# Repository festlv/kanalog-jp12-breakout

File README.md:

KFlop KAnalog JP12 breakout
==================================

KAnalog board has a connector JP12 with 8 outputs and 8 inputs. Since these IOs are unprotected, 3.3V LVTTL type, they 
are less than suitable for use for general purpose tasks (extra end stops, outputs etc).

This board breaks out these IOs as opto-isolated inputs and outputs, suitable for driving 24V loads and reading 24V inputs.

IO connection follows Kconnect conventions, see optoisolated inputs/outputs section of [this document](http://dynomotion.com/Help/SchematicsKonnect/ConnectorsKonnect.htm).

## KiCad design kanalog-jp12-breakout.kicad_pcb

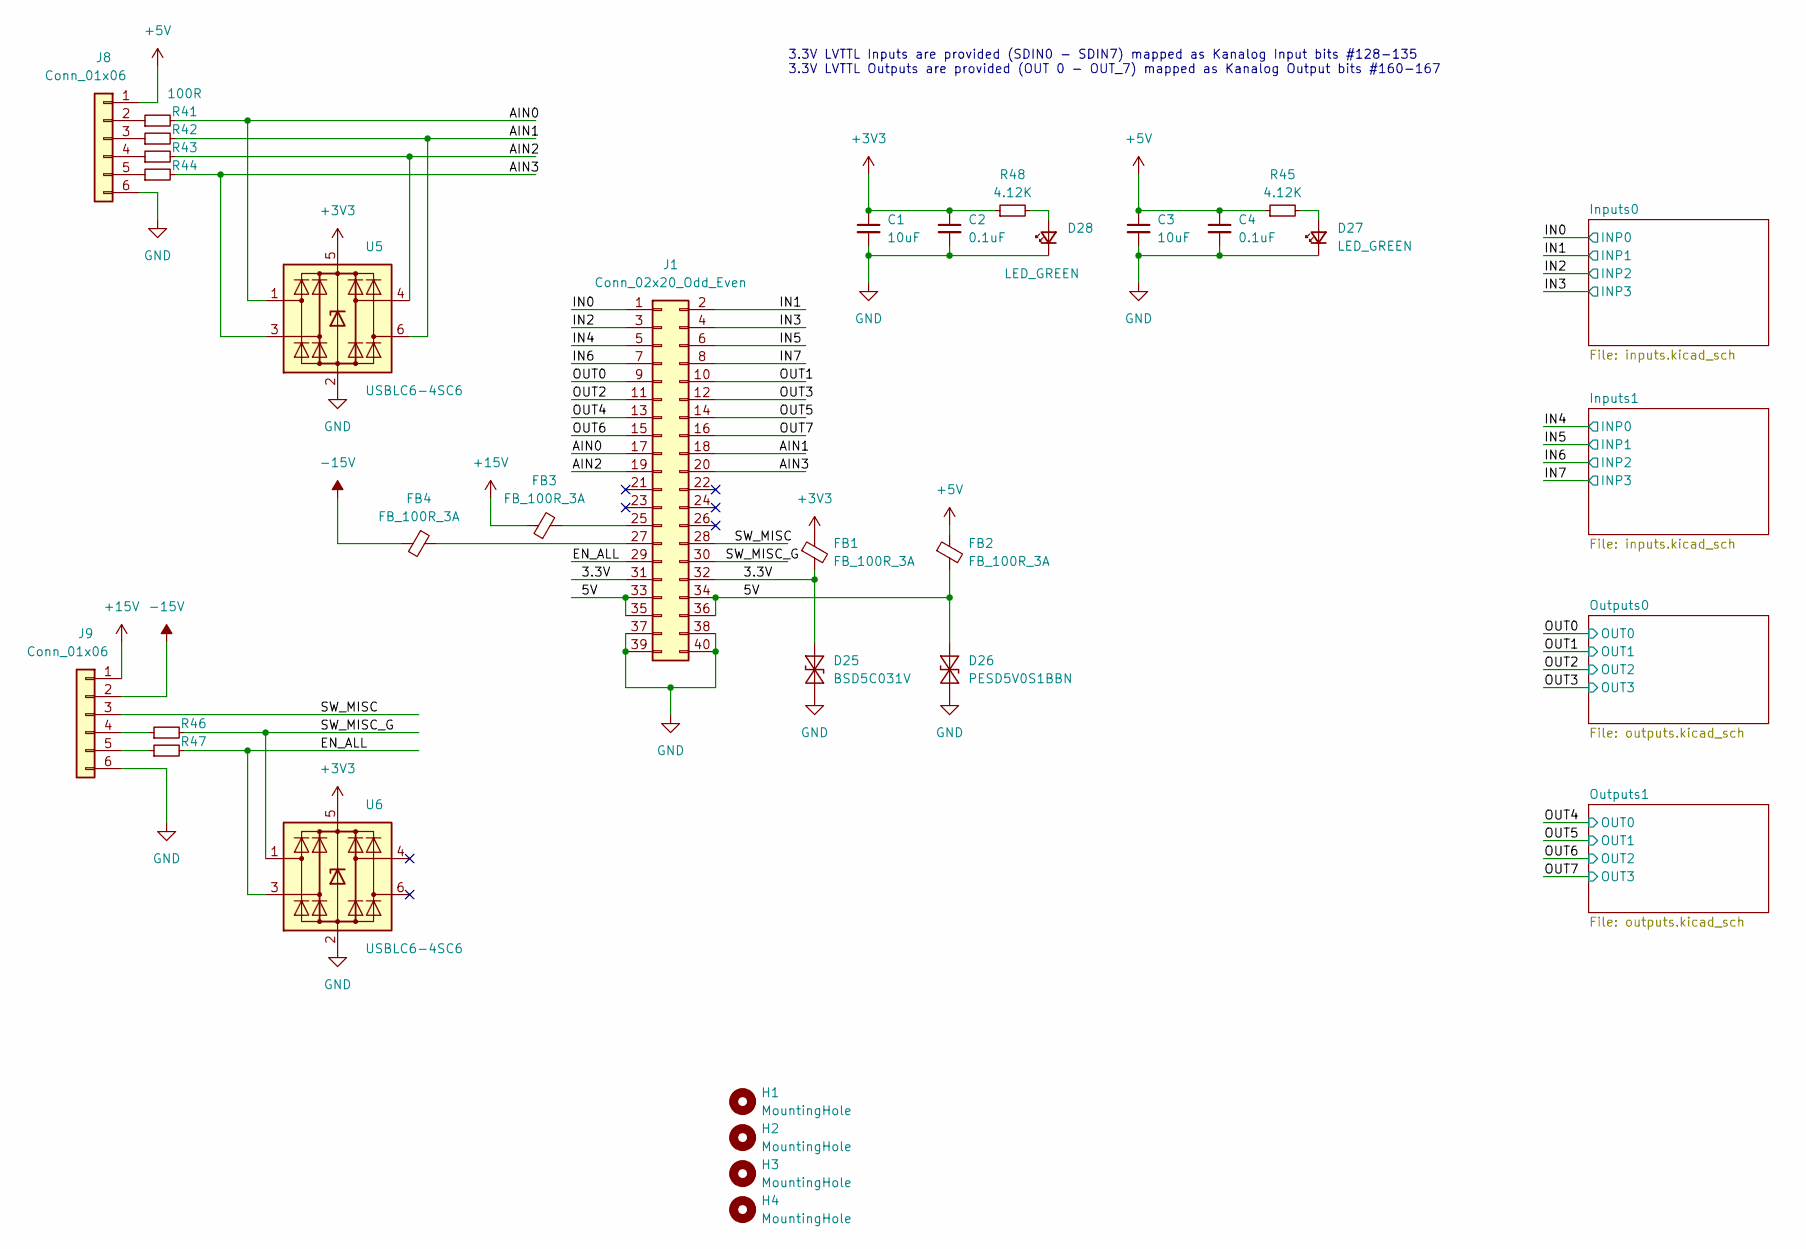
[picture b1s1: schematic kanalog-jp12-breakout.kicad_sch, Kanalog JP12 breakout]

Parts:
C1, C3: 10uF; C_0805_2012Metric; MPN CL21A106KPFNNNE; LCSC# C17024
C2, C4: 0.1uF; C_0603_1608Metric
D25: BSD5C031V; D_SOD-523; MPN BSD5C031V; LCSC# C151984
D26: PESD5V0S1BBN; D_SOD-523; MPN PESD5V0S1BBN; LCSC# C314264
D27, D28: LED_GREEN; LED_0603_1608Metric; MPN SZYY0603YG; LCSC# C434423
FB1, FB2, FB3, FB4: FB_100R_3A; L_0603_1608Metric; MPN UPZ1608E101-3R0TF; LCSC# C96995
H1, H2, H3, H4: MountingHole; MountingHole_3.5mm
J1: Conn_02x20_Odd_Even; IDC-Header_2x20_P2.54mm_Vertical; MPN X1270WR-2x20A-6TV01; LCSC# C2962248
J8, J9: Conn_01x06; PinHeader_1x06_P2.54mm_Vertical
R41, R42, R43, R44, R46, R47: 100R; R_0603_1608Metric; MPN 0603WAF1000T5E; LCSC# C22775
R45, R48: 4.12K; R_0603_1608Metric; MPN 0603WAF4121T5E; LCSC# C23041
U5, U6: USBLC6-4SC6; SOT-23-6; MPN USBLC6-4SC6; LCSC# C5197386

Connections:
+3V3: C1.1, C2.1, FB1.1, R48.1, U5.5 (VBUS), U6.5 (VBUS); also elsewhere on the board
+5V: C3.1, C4.1, FB2.1, J8.1, R45.1; also elsewhere on the board
+15V: FB3.1, J9.1
-15V: FB4.2, J9.2
/3.3V: D25.2 (A2), FB1.2, J1.31, J1.32
/5V: D26.2 (A2), FB2.2, J1.33, J1.34, J1.35, J1.36
/AIN0: J1.17, R41.2, U5.1 (I/O1)
/AIN1: J1.18, R42.2, U5.6 (I/O4)
/AIN2: J1.19, R43.2, U5.4 (I/O3)
/AIN3: J1.20, R44.2, U5.3 (I/O2)
/EN_ALL: J1.29, R47.2, U6.3 (I/O2)
/IN0: J1.1; also elsewhere on the board
/IN1: J1.2; also elsewhere on the board
/IN2: J1.3; also elsewhere on the board
/IN3: J1.4; also elsewhere on the board
/IN4: J1.5; also elsewhere on the board
/IN5: J1.6; also elsewhere on the board
/IN6: J1.7; also elsewhere on the board
/IN7: J1.8; also elsewhere on the board
/OUT0: J1.9; also elsewhere on the board
/OUT1: J1.10; also elsewhere on the board
/OUT2: J1.11; also elsewhere on the board
/OUT3: J1.12; also elsewhere on the board
/OUT4: J1.13; also elsewhere on the board
/OUT5: J1.14; also elsewhere on the board
/OUT6: J1.15; also elsewhere on the board
/OUT7: J1.16; also elsewhere on the board
/SW_MISC: J1.28, J9.3
/SW_MISC_G: J1.30, R46.2, U6.1 (I/O1)
GND: C1.2, C2.2, C3.2, C4.2, D25.1 (A1), D26.1 (A1), D27.1 (K), D28.1 (K), J1.37, J1.38, J1.39, J1.40, J8.6, J9.6, U5.2 (GND), U6.2 (GND); also elsewhere on the board
unnamed: D27.2 (A), R45.2
unnamed: D28.2 (A), R48.2
unnamed: FB3.2, J1.25
unnamed: FB4.1, J1.27
unnamed: J8.2, R41.1
unnamed: J8.3, R42.1
unnamed: J8.4, R43.1
unnamed: J8.5, R44.1
unnamed: J9.4, R46.1
unnamed: J9.5, R47.1

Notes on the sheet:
3.3V LVTTL Inputs are provided (SDIN0 - SDIN7) mapped as Kanalog Input bits #128-135 3.3V LVTTL Outputs are provided (OUT 0 - OUT_7) mapped as Kanalog Output bits #160-167

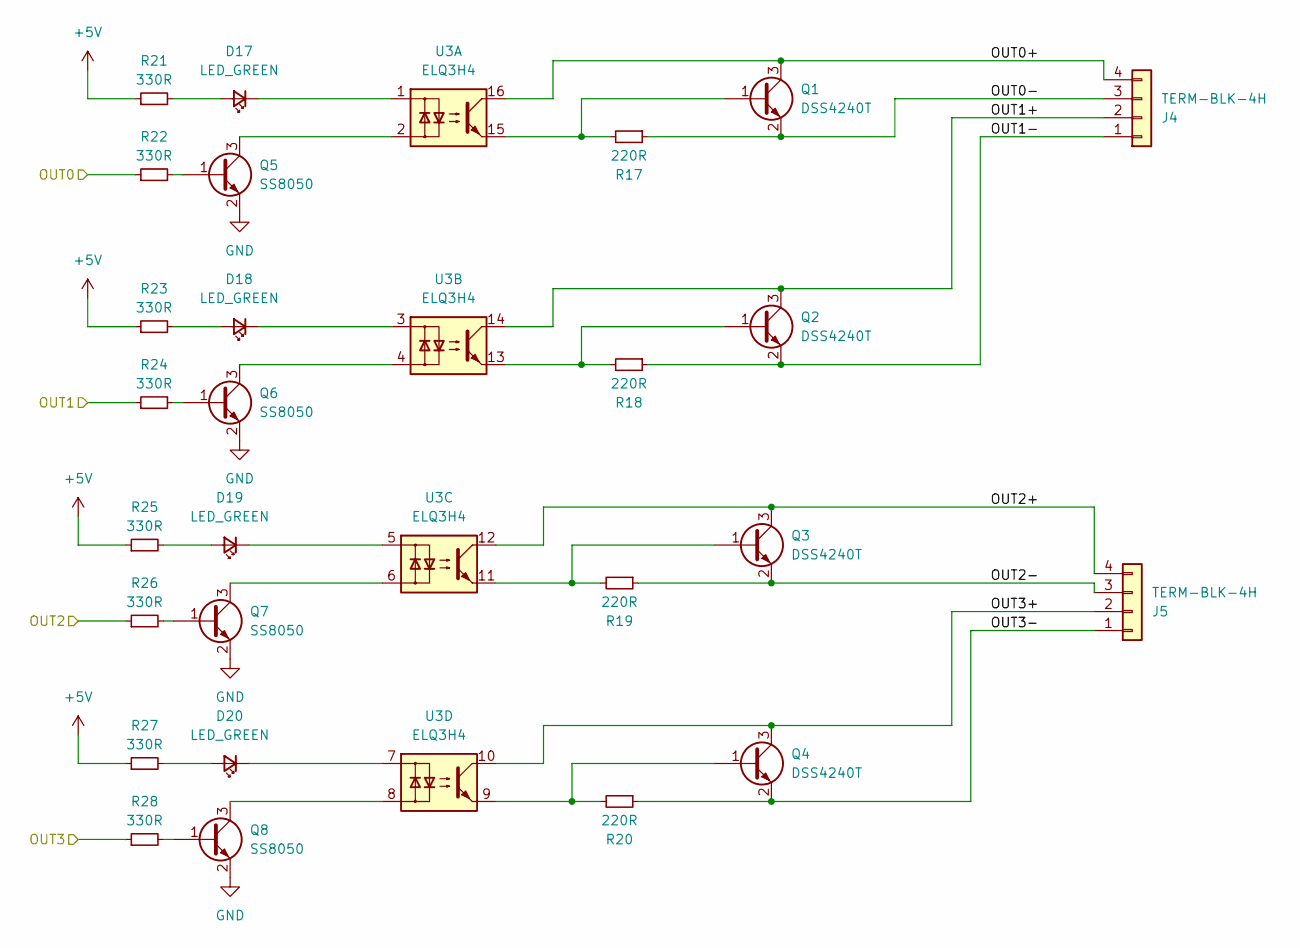
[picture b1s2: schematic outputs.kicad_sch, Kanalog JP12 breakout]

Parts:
D17, D18, D19, D20: LED_GREEN; LED_0603_1608Metric; MPN SZYY0603YG; LCSC# C434423
J4, J5: TERM-BLK-4H; PhoenixContact_MC_1,5_4-G-3.5_1x04_P3.50mm_Horizontal; MPN KF2EDGR-3.5-4P; LCSC# C441173
Q1, Q2, Q3, Q4: DSS4240T; SOT-23; MPN DSS4240T-7; LCSC# C151399
Q5, Q6, Q7, Q8: SS8050; SOT-23; MPN SS8050; LCSC# C2150
R17, R18, R19, R20: 220R; R_0603_1608Metric; MPN 0603WAF2200T5E; LCSC# C22962
R21, R22, R23, R24, R25, R26, R27, R28: 330R; R_0603_1608Metric; MPN 0603WAF3300T5E; LCSC# C23138
U3: ELQ3H4; SOIC-16W_5.3x10.2mm_P1.27mm; MPN ELQ3H4(TA)-G; LCSC# C150957

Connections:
+5V: R21.1, R23.1, R25.1, R27.1; also elsewhere on the board
/OUT0: R22.1; also elsewhere on the board
/OUT1: R24.1; also elsewhere on the board
/OUT2: R26.1; also elsewhere on the board
/OUT3: R28.1; also elsewhere on the board
/Outputs0/OUT0+: J4.4, Q1.3 (C), U3.16
/Outputs0/OUT0-: J4.3, Q1.2 (E), R17.1
/Outputs0/OUT1+: J4.2, Q2.3 (C), U3.14
/Outputs0/OUT1-: J4.1, Q2.2 (E), R18.1
/Outputs0/OUT2+: J5.4, Q3.3 (C), U3.12
/Outputs0/OUT2-: J5.3, Q3.2 (E), R19.1
/Outputs0/OUT3+: J5.2, Q4.3 (C), U3.10
/Outputs0/OUT3-: J5.1, Q4.2 (E), R20.1
GND: Q5.2 (E), Q6.2 (E), Q7.2 (E), Q8.2 (E); also elsewhere on the board
unnamed: D17.2 (A), R21.2
unnamed: D17.1 (K), U3.1
unnamed: D18.2 (A), R23.2
unnamed: D18.1 (K), U3.3
unnamed: D19.2 (A), R25.2
unnamed: D19.1 (K), U3.5
unnamed: D20.2 (A), R27.2
unnamed: D20.1 (K), U3.7
unnamed: Q1.1 (B), R17.2, U3.15
unnamed: Q2.1 (B), R18.2, U3.13
unnamed: Q3.1 (B), R19.2, U3.11
unnamed: Q4.1 (B), R20.2, U3.9
unnamed: Q5.1 (B), R22.2
unnamed: Q5.3 (C), U3.2
unnamed: Q6.1 (B), R24.2
unnamed: Q6.3 (C), U3.4
unnamed: Q7.1 (B), R26.2
unnamed: Q7.3 (C), U3.6
unnamed: Q8.1 (B), R28.2
unnamed: Q8.3 (C), U3.8

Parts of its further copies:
D21, D22, D23, D24: LED_GREEN; LED_0603_1608Metric; MPN SZYY0603YG; LCSC# C434423
J6, J7: TERM-BLK-4H; PhoenixContact_MC_1,5_4-G-3.5_1x04_P3.50mm_Horizontal; MPN KF2EDGR-3.5-4P; LCSC# C441173
Q9, Q10, Q11, Q12: SS8050; SOT-23; MPN SS8050; LCSC# C2150
Q13, Q14, Q15, Q16: DSS4240T; SOT-23; MPN DSS4240T-7; LCSC# C151399
R29, R30, R31, R32, R33, R34, R35, R36: 330R; R_0603_1608Metric; MPN 0603WAF3300T5E; LCSC# C23138
R37, R38, R39, R40: 220R; R_0603_1608Metric; MPN 0603WAF2200T5E; LCSC# C22962
U4: ELQ3H4; SOIC-16W_5.3x10.2mm_P1.27mm; MPN ELQ3H4(TA)-G; LCSC# C150957

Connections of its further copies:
+5V: R29.1, R31.1, R33.1, R35.1; also elsewhere on the board
/OUT4: R34.1; also elsewhere on the board
/OUT5: R36.1; also elsewhere on the board
/OUT6: R30.1; also elsewhere on the board
/OUT7: R32.1; also elsewhere on the board
/Outputs1/OUT0+: J7.4, Q15.3 (C), U4.16
/Outputs1/OUT0-: J7.3, Q15.2 (E), R39.1
/Outputs1/OUT1+: J7.2, Q16.3 (C), U4.14
/Outputs1/OUT1-: J7.1, Q16.2 (E), R40.1
/Outputs1/OUT2+: J6.4, Q13.3 (C), U4.12
/Outputs1/OUT2-: J6.3, Q13.2 (E), R37.1
/Outputs1/OUT3+: J6.2, Q14.3 (C), U4.10
/Outputs1/OUT3-: J6.1, Q14.2 (E), R38.1
GND: Q9.2 (E), Q10.2 (E), Q11.2 (E), Q12.2 (E); also elsewhere on the board
unnamed: D21.2 (A), R29.2
unnamed: D21.1 (K), U4.5
unnamed: D22.2 (A), R31.2
unnamed: D22.1 (K), U4.7
unnamed: D23.2 (A), R33.2
unnamed: D23.1 (K), U4.1
unnamed: D24.2 (A), R35.2
unnamed: D24.1 (K), U4.3
unnamed: Q9.1 (B), R30.2
unnamed: Q9.3 (C), U4.6
unnamed: Q10.1 (B), R32.2
unnamed: Q10.3 (C), U4.8
unnamed: Q11.1 (B), R34.2
unnamed: Q11.3 (C), U4.2
unnamed: Q12.1 (B), R36.2
unnamed: Q12.3 (C), U4.4
unnamed: Q13.1 (B), R37.2, U4.11
unnamed: Q14.1 (B), R38.2, U4.9
unnamed: Q15.1 (B), R39.2, U4.15
unnamed: Q16.1 (B), R40.2, U4.13

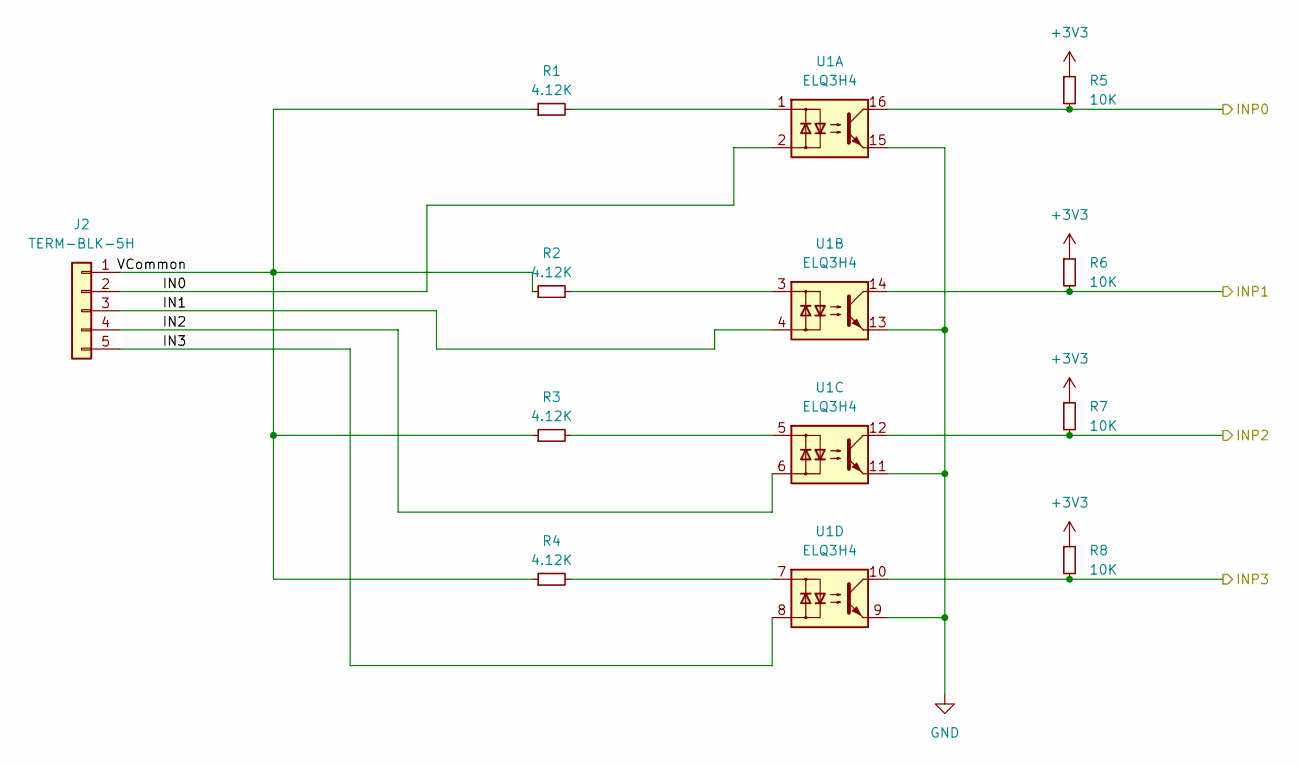
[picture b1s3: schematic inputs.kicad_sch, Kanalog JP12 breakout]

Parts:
J2: TERM-BLK-5H; PhoenixContact_MC_1,5_5-G-3.5_1x05_P3.50mm_Horizontal; MPN KF2EDGR-3.5-5P; LCSC# C441174
R1, R2, R3, R4: 4.12K; R_0603_1608Metric; MPN 0603WAF4121T5E; LCSC# C23041
R5, R6, R7, R8: 10K; R_0603_1608Metric; MPN 0603WAF1002T5E; LCSC# C25804
U1: ELQ3H4; SOIC-16W_5.3x10.2mm_P1.27mm; MPN ELQ3H4(TA)-G; LCSC# C150957

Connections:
+3V3: R5.1, R6.1, R7.1, R8.1; also elsewhere on the board
/IN0: R5.2, U1.16; also elsewhere on the board
/IN1: R6.2, U1.14; also elsewhere on the board
/IN2: R7.2, U1.12; also elsewhere on the board
/IN3: R8.2, U1.10; also elsewhere on the board
/Inputs0/IN0: J2.2, U1.2
/Inputs0/IN1: J2.3, U1.4
/Inputs0/IN2: J2.4, U1.6
/Inputs0/IN3: J2.5, U1.8
/Inputs0/VCommon: J2.1, R1.1, R2.1, R3.1, R4.1
GND: U1.9, U1.11, U1.13, U1.15; also elsewhere on the board
unnamed: R1.2, U1.1
unnamed: R2.2, U1.3
unnamed: R3.2, U1.5
unnamed: R4.2, U1.7

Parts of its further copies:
J3: TERM-BLK-5H; PhoenixContact_MC_1,5_5-G-3.5_1x05_P3.50mm_Horizontal; MPN KF2EDGR-3.5-5P; LCSC# C441174
R9, R10, R11, R12: 4.12K; R_0603_1608Metric; MPN 0603WAF4121T5E; LCSC# C23041
R13, R14, R15, R16: 10K; R_0603_1608Metric; MPN 0603WAF1002T5E; LCSC# C25804
U2: ELQ3H4; SOIC-16W_5.3x10.2mm_P1.27mm; MPN ELQ3H4(TA)-G; LCSC# C150957

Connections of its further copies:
+3V3: R13.1, R14.1, R15.1, R16.1; also elsewhere on the board
/IN4: R13.2, U2.16; also elsewhere on the board
/IN5: R14.2, U2.14; also elsewhere on the board
/IN6: R15.2, U2.12; also elsewhere on the board
/IN7: R16.2, U2.10; also elsewhere on the board
/Inputs1/IN0: J3.2, U2.2
/Inputs1/IN1: J3.3, U2.4
/Inputs1/IN2: J3.4, U2.6
/Inputs1/IN3: J3.5, U2.8
/Inputs1/VCommon: J3.1, R9.1, R10.1, R11.1, R12.1
GND: U2.9, U2.11, U2.13, U2.15; also elsewhere on the board
unnamed: R9.2, U2.1
unnamed: R10.2, U2.3
unnamed: R11.2, U2.5
unnamed: R12.2, U2.7

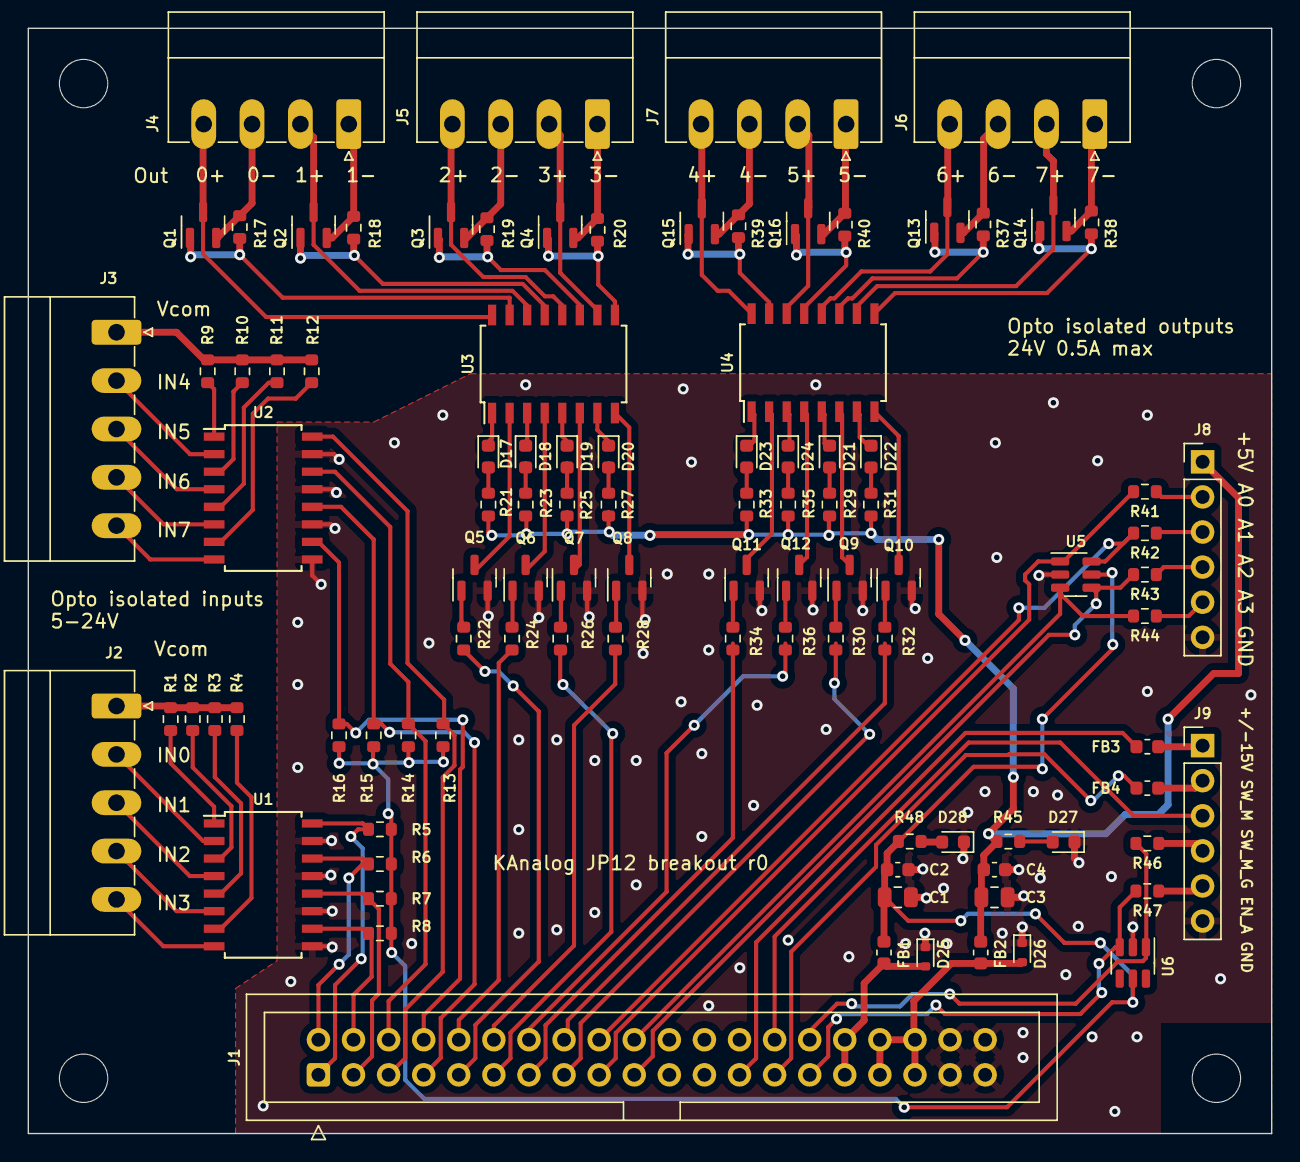
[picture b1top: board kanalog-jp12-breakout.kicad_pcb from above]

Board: 2 copper layers, 90.0 x 80.0 mm, 103 parts (0 on the bottom side), 114 nets.

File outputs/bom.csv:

"Source:","/home/reinis/Sync/ee/kanalog-jp12-breakout/kanalog-jp12-breakout.kicad_sch"
"Date:","trešdiena, 2023. gada 31. maijs, 02:11:31"
"Tool:","Eeschema 7.0.5-4d25ed1034~172~ubuntu20.04.1"
"Generator:","/usr/share/kicad/plugins/bom_csv_grouped_by_value.py"
"Component Count:","99"

"Collated Components:"

"Item","Qty","Reference(s)","Value","LibPart","Footprint","Datasheet","DNP","LCSC#","MPN","Manufacturer"
"1","2","C1, C3","10uF","Device:C_Small","Capacitor_SMD:C_0805_2012Metric","~","","C17024","CL21A106KPFNNNE","Samsung"
"2","2","C2, C4","0.1uF","Device:C_Small","Capacitor_SMD:C_0603_1608Metric","~","","","",""
"3","10","D17, D18, D19, D20, D21, D22, D23, D24, D27, D28","LED_GREEN","hadv-ui:LED_GREEN","LED_SMD:LED_0603_1608Metric","~","","C434423","SZYY0603YG","Yongyu Photoelectric"
"4","1","D25","BSD5C031V","hadv-protection:BSD5C031V","Diode_SMD:D_SOD-523","https://datasheet.lcsc.com/lcsc/1912111437_BORN-BSD5C031V_C1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","","C151984","BSD5C031V","BORN"
"5","1","D26","PESD5V0S1BBN","hadv-protection:PESD5V0S1BBN","Diode_SMD:D_SOD-523","https://datasheet.lcsc.com/lcsc/1912111437_BORN-PESD5V0S1BBN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","","C314264","PESD5V0S1BBN","BORN"
"6","4","FB1, FB2, FB3, FB4","FB_100R_3A","hadv-passives:FB_100R_3A","Inductor_SMD:L_0603_1608Metric","~","","C96995","UPZ1608E101-3R0TF","Sunlord"
"7","1","J1","Conn_02x20_Odd_Even","Connector_Generic:Conn_02x20_Odd_Even","Connector_IDC:IDC-Header_2x20_P2.54mm_Vertical","~","","C2962248","X1270WR-2x20A-6TV01","XKB"
"8","2","J2, J3","TERM-BLK-5H","hadv-connectors:TERM-BLK-5H","Connector_Phoenix_MC:PhoenixContact_MC_1,5_5-G-3.5_1x05_P3.50mm_Horizontal","~","","C441174","KF2EDGR-3.5-5P","Cixi Kefa Elec"
"9","4","J4, J5, J6, J7","TERM-BLK-4H","hadv-connectors:TERM-BLK-4H","Connector_Phoenix_MC:PhoenixContact_MC_1,5_4-G-3.5_1x04_P3.50mm_Horizontal","~","","C441173","KF2EDGR-3.5-4P","Cixi Kefa Elec"
"10","2","J8, J9","Conn_01x06","Connector_Generic:Conn_01x06","Connector_PinHeader_2.54mm:PinHeader_1x06_P2.54mm_Vertical","~","","","",""
"11","8","Q1, Q2, Q3, Q4, Q13, Q14, Q15, Q16","DSS4240T","hadv-transistors:DSS4240T","Package_TO_SOT_SMD:SOT-23","https://datasheet.lcsc.com/lcsc/1809081612_Diodes-Incorporat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","","C151399","DSS4240T-7","Diodes Inc"
"12","8","Q5, Q6, Q7, Q8, Q9, Q10, Q11, Q12","SS8050","hadv-transistors:SS8050","Package_TO_SOT_SMD:SOT-23","~","","C2150","SS8050","Jiangsu Changjing Electronics"
"13","10","R1, R2, R3, R4, R9, R10, R11, R12, R45, R48","4.12K","Device:R_Small","Resistor_SMD:R_0603_1608Metric","~","","C23041","0603WAF4121T5E","Uniroyal"
"14","8","R5, R6, R7, R8, R13, R14, R15, R16","10K","Device:R_Small","Resistor_SMD:R_0603_1608Metric","~","","C25804","0603WAF1002T5E","Uniroyal"
"15","8","R17, R18, R19, R20, R37, R38, R39, R40","220R","Device:R_Small","Resistor_SMD:R_0603_1608Metric","~","","C22962","0603WAF2200T5E","Uniroyal"
"16","16","R21, R22, R23, R24, R25, R26, R27, R28, R29, R30, R31, R32, R33, R34, R35, R36","330R","Device:R_Small","Resistor_SMD:R_0603_1608Metric","~","","C23138","0603WAF3300T5E","Uniroyal"
"17","6","R41, R42, R43, R44, R46, R47","100R","Device:R_Small","Resistor_SMD:R_0603_1608Metric","~","","C22775","0603WAF1000T5E","Uniroyal"
"18","4","U1, U2, U3, U4","ELQ3H4","hadv-buffers-translators:ELQ3H4","Package_SO:SOIC-16W_5.3x10.2mm_P1.27mm","https://datasheet.lcsc.com/lcsc/1810301025_Everlight-Elec-EL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","","C150957","ELQ3H4(TA)-G","Everlight Elec"
"19","2","U5, U6","USBLC6-4SC6","hadv-protection:USBLC6-4SC6","Package_TO_SOT_SMD:SOT-23-6","https://www.st.com/resource/en/datasheet/usblc6-4.pdf","","C5197386","USBLC6-4SC6","TECH PUBLIC"

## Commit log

2023-05-30 Initial commit of rev0
2023-05-30 Add readme
